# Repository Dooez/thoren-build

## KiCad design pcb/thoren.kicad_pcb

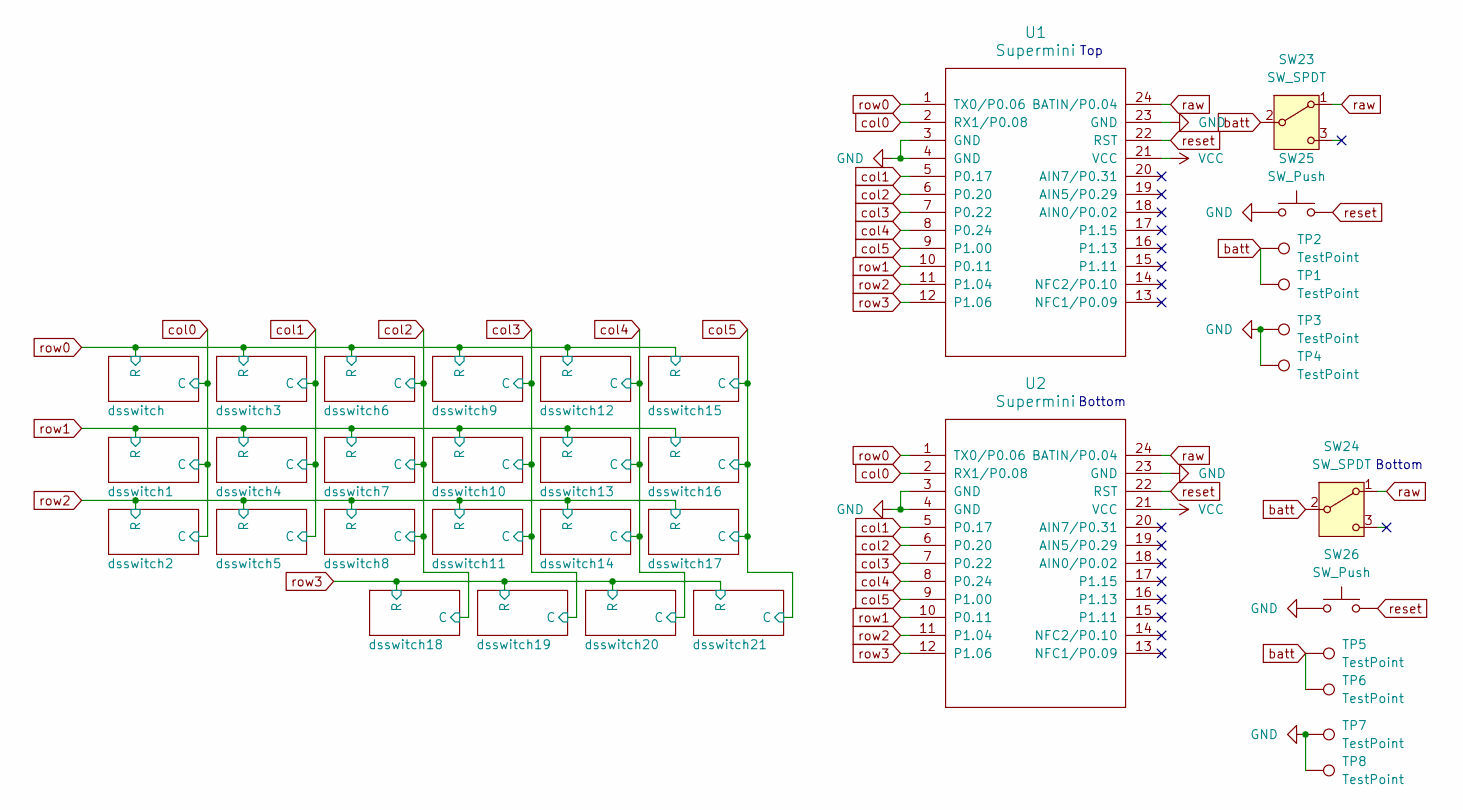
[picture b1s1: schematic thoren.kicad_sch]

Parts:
SW23, SW24: SW_SPDT; switch_SSSS811101
SW25, SW26: SW_Push; SW_Push_1P1T-MP_NO_Horizontal_Alps_SKRTLAE010
TP1, TP2, TP5, TP6: TestPoint; TestPoint_Pad_D2.0mm
TP3, TP4, TP7, TP8: TestPoint; TestPoint_Pad_2.0x2.0mm
U1, U2: Supermini; Supermini face up left smd socket

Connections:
GND: SW25.1, SW26.1, TP3.1, TP4.1, TP7.1, TP8.1, U1.3 (GND), U1.4 (GND), U1.23 (GND), U2.3 (GND), U2.4 (GND), U2.23 (GND)
VCC: U1.21 (VCC), U2.21 (VCC)
batt: SW23.2 (B), SW24.2 (B), TP1.1, TP2.1, TP5.1, TP6.1
col0: U1.2 (RX1/P0.08), U2.2 (RX1/P0.08); also elsewhere on the board
col1: U1.5 (P0.17), U2.5 (P0.17); also elsewhere on the board
col2: U1.6 (P0.20), U2.6 (P0.20); also elsewhere on the board
col3: U1.7 (P0.22), U2.7 (P0.22); also elsewhere on the board
col4: U1.8 (P0.24), U2.8 (P0.24); also elsewhere on the board
col5: U1.9 (P1.00), U2.9 (P1.00); also elsewhere on the board
raw: SW23.1 (A), SW24.1 (A), U1.24 (BATIN/P0.04), U2.24 (BATIN/P0.04)
reset: SW25.2, SW26.2, U1.22 (RST), U2.22 (RST)
row0: U1.1 (TX0/P0.06), U2.1 (TX0/P0.06); also elsewhere on the board
row1: U1.10 (P0.11), U2.10 (P0.11); also elsewhere on the board
row2: U1.11 (P1.04), U2.11 (P1.04); also elsewhere on the board
row3: U1.12 (P1.06), U2.12 (P1.06); also elsewhere on the board

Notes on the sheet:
Bottom
Top

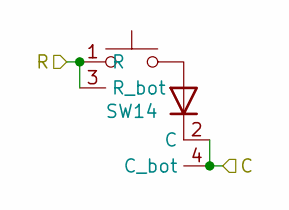
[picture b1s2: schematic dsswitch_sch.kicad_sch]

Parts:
SW14: choc_hotswap_18_17_sod123

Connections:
col4: SW14.2 (C), SW14.4 (C_bot); also elsewhere on the board
row1: SW14.1 (R), SW14.3 (R_bot); also elsewhere on the board

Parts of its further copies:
SW1, SW2, SW3, SW4, SW5, SW6, SW7, SW8, SW9, SW10, SW11, SW12, SW13, SW15, SW16, SW17, SW18, SW19, SW20, SW21, SW22: choc_hotswap_18_17_sod123

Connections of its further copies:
col0: SW1.2 (C), SW1.4 (C_bot), SW2.2 (C), SW2.4 (C_bot), SW3.2 (C), SW3.4 (C_bot); also elsewhere on the board
col1: SW4.2 (C), SW4.4 (C_bot), SW5.2 (C), SW5.4 (C_bot), SW6.2 (C), SW6.4 (C_bot); also elsewhere on the board
col2: SW7.2 (C), SW7.4 (C_bot), SW8.2 (C), SW8.4 (C_bot), SW9.2 (C), SW9.4 (C_bot), SW19.2 (C), SW19.4 (C_bot); also elsewhere on the board
col3: SW10.2 (C), SW10.4 (C_bot), SW11.2 (C), SW11.4 (C_bot), SW12.2 (C), SW12.4 (C_bot), SW20.2 (C), SW20.4 (C_bot); also elsewhere on the board
col4: SW13.2 (C), SW13.4 (C_bot), SW15.2 (C), SW15.4 (C_bot), SW21.2 (C), SW21.4 (C_bot); also elsewhere on the board
col5: SW16.2 (C), SW16.4 (C_bot), SW17.2 (C), SW17.4 (C_bot), SW18.2 (C), SW18.4 (C_bot), SW22.2 (C), SW22.4 (C_bot); also elsewhere on the board
row0: SW1.1 (R), SW1.3 (R_bot), SW4.1 (R), SW4.3 (R_bot), SW7.1 (R), SW7.3 (R_bot), SW10.1 (R), SW10.3 (R_bot), SW13.1 (R), SW13.3 (R_bot), SW16.1 (R), SW16.3 (R_bot); also elsewhere on the board
row1: SW2.1 (R), SW2.3 (R_bot), SW5.1 (R), SW5.3 (R_bot), SW8.1 (R), SW8.3 (R_bot), SW11.1 (R), SW11.3 (R_bot), SW17.1 (R), SW17.3 (R_bot); also elsewhere on the board
row2: SW3.1 (R), SW3.3 (R_bot), SW6.1 (R), SW6.3 (R_bot), SW9.1 (R), SW9.3 (R_bot), SW12.1 (R), SW12.3 (R_bot), SW15.1 (R), SW15.3 (R_bot), SW18.1 (R), SW18.3 (R_bot); also elsewhere on the board
row3: SW19.1 (R), SW19.3 (R_bot), SW20.1 (R), SW20.3 (R_bot), SW21.1 (R), SW21.3 (R_bot), SW22.1 (R), SW22.3 (R_bot); also elsewhere on the board

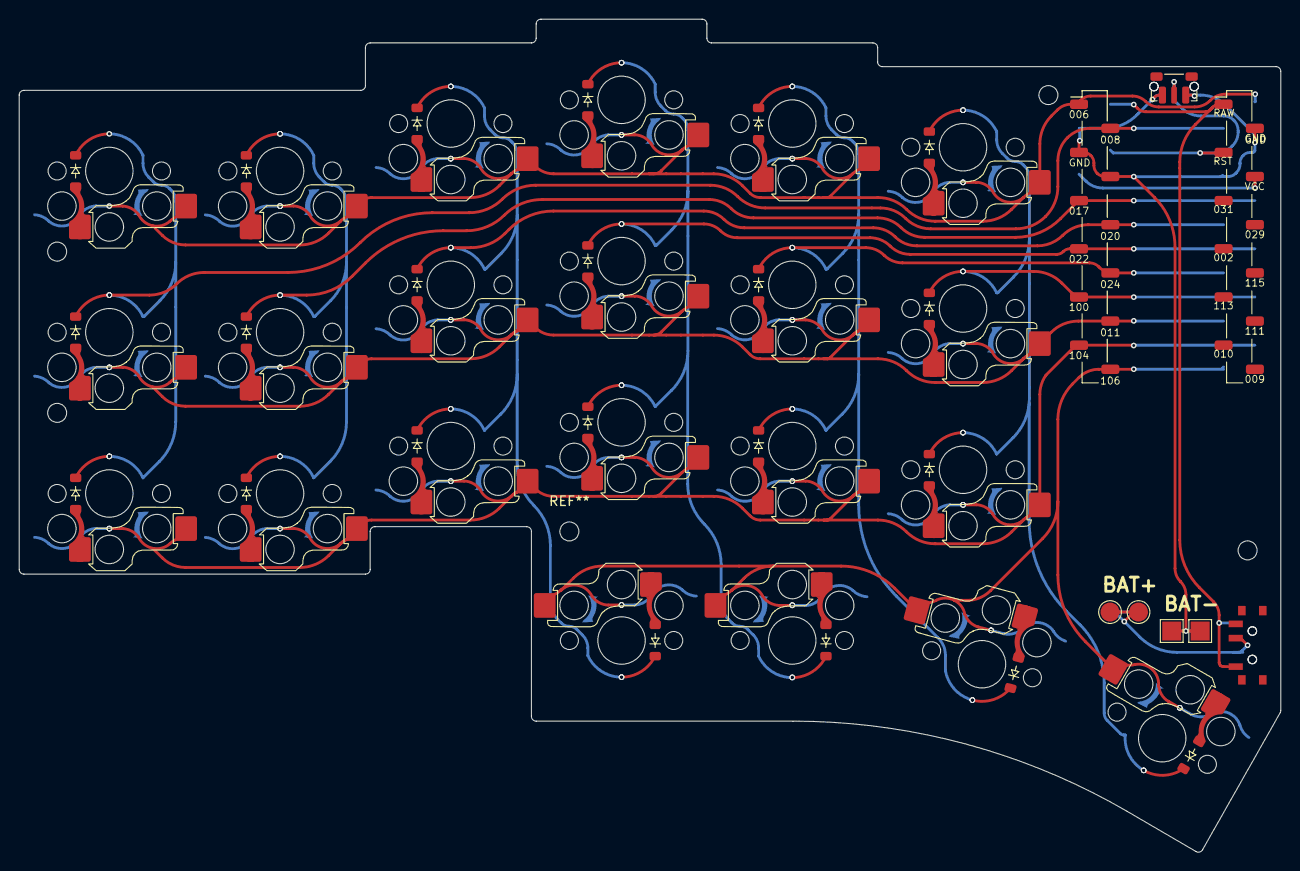
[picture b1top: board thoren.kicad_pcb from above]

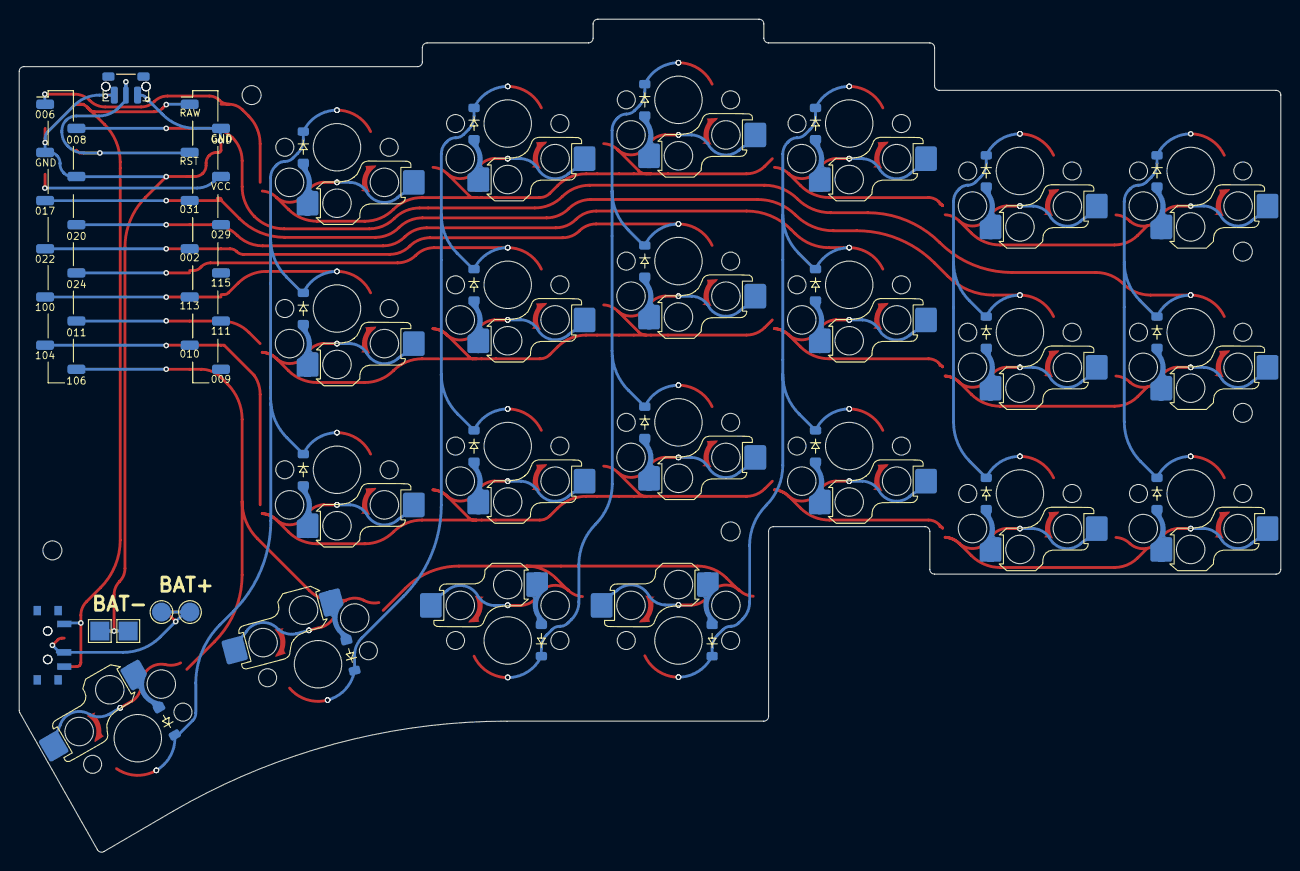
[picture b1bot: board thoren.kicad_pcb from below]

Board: 2 copper layers, 133.0 x 87.8 mm, 36 parts (11 on the bottom side), 15 nets.

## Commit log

2025-01-14 First commit.
2025-01-14 Rename thoren.md to index.md
2025-01-14 First draft.
2025-01-14 Fix images and some text editing.
2025-01-15 Added youtube embed.
2025-01-15 Small writing.
2025-01-15 Some edits.
2025-01-28 Added missing pictures.
2025-01-28 Added hardware.
2025-01-28 Update text with new picture.
2025-01-28 Added missing step and link.
